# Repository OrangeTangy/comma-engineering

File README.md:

# comma.ai engineering portfolio — work in progress

This folder contains AI-assisted source, experiments and measured results for
the PCBGolf and original-CAN-core requests. **Neither requested project is
complete. These are work-in-progress portfolio artifacts, not a finalized
PCBGolf solution. No board has been fabricated or tested on hardware.**

## Reviewer entry points

- [Submission status and reproducibility](SUBMISSION.md): current evidence and known failures.
- [Classical CAN RTL and tests](can-core/README.md): simulation-tested bit-level engines.
- [PCBGolf layout experiments](pcbgolf/README.md): native KiCad projects and assembly exports.
- [Verification status](reports/STATUS.md): explicit completion gates.

## What works now

- `WORKING_PROMPT.md`: the prompt applied to guide the work.
- `can-core/`: original transmit/receive SystemVerilog bit-level engines, an
  independent polynomial-division Python oracle and deterministic simulation tests.
- `pcbgolf/`: source inventory, deterministic placement experiment, unchanged
  libraries, integrated schematics and editable KiCad placement/routing trials.
- `reports/`: tool logs and project status.

The CAN simulation suite passed 2,386 cases: 777 valid receive vectors, 770
transmit vectors, 496 receive fault/recovery cases, 100 back-to-back frames,
127 reset positions, 113 arbitration scenarios and three transmitter faults.
Twenty-six receive cases exercise a stuff bit immediately after the CRC sequence.
These are simulation results, not hardware or ISO compliance claims. Both RTL
modules also passed generic Yosys synthesis and structural checks with no
reported problems. FPGA mapping/timing remain unverified; see reports/STATUS.md.

The PCB placement experiment produced a 70 × 60 mm outline with all 245 original
footprints and their pad/net assignments retained. Its all-net half-perimeter
wirelength proxy decreased from 10,780.574 to 7,685.120 mm (28.71%). That is an
optimization of a proxy, **not a reduction in measured board score**. It has
zero routed tracks. Native KiCad now works: an assembly STEP was exported and
measured at 70 × 60 × 12.595 mm. This is an unrouted geometry measurement, not
a valid contest score. The integrated routing trial has repaired schematic
hierarchy and zero schematic/PCB parity errors; 499 unconnected items remain.

## Blocking completion

PCB: KiCad 10.0.6 runs from the local tools directory. The candidate still needs
mechanical/functional placement review, complete routing, native ERC/DRC,
fabrication-rule checks, assembly collision checks and an actual score. A leaderboard
entry would be misleading at this stage. Published prize deadline: October 12,
2026; current date: October 20. Late leaderboard acceptance is unconfirmed.

CAN: the core still needs bit timing/resynchronization, integrated bus access,
error frames/confinement/recovery, register/FIFO interface and FPGA constraints.
Extended CAN and CAN-FD are not implemented. No hardware is available.

The experiments suggest follow-up hypotheses, but an online search did not
establish that either is new. Existing work already includes AI placement,
autorouting, multi-board stacking and aggressive connector changes.

## Cheapest hardware starting point

As checked October 15, 2026: Tang Nano 9K was listed at $14.90 by Seeed, but out
of stock. It is a low-cost candidate for developing a small original controller;
a complete future CAN-FD design's fit and timing have not been established.
Sipeed documents its 8,640 LUT4 resources and onboard programming interface.
A Waveshare SN65HVD230 3.3 V Classical-CAN transceiver board was listed at $4.99.
That is about $20 excluding shipping, wiring and a second independent CAN node.
The SN65HVD230 is not the choice for validating high-rate CAN-FD.

Start with free simulation. Confirm FPGA fit and available seller inventory
before buying. Buy a CAN **transceiver** for the FPGA, not an MCP2515 controller
module that would implement the protocol externally. An independent MCU CAN
node or USB-CAN adapter is useful later as a reference peer.

Sources:
- https://wiki.sipeed.com/hardware/en/tang/Tang-Nano-9K/Nano-9K.html
- https://www.seeedstudio.com/tag/FPGA-Development-Board.html
- https://www.waveshare.com/product/sn65hvd230-can-board.htm
- https://github.com/commaai/PCBGolf
- https://comma.ai/leaderboard
- https://github.com/Logic-Design-Services/CTU-CAN-FD

## Application use

Do not describe this as a completed contest entry or an independently built,
production-ready CAN-FD controller. A defensible current description is:
“Developing an AI-assisted Classical CAN RTL prototype; I am reproducing and
reviewing its fault-injection tests and extending it toward hardware validation.”
Use that wording only after you have actually reproduced/reviewed the tests.
The final application should explain your own decisions, measurements and
contributions, with AI assistance disclosed accurately. No application email
has been prepared or sent.

Latest work (October 20): `pcbgolf/critical-trial/` groups 47 components by
circuit on the underside. It shortens critical switcher/clock pad distances and
has zero schematic-parity issues, but all 499 connections remain unrouted.
Its assembly envelope is 70.4 × 60.4 × 14.230 mm. The old placement's separate
`partial-route/` contains an incomplete routing diagnostic with 339 unconnected
items and six width violations. Neither is fabrication-ready or a submission.

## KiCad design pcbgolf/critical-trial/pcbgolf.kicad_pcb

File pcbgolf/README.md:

# PCBGolf engineering study

**Not a submission. No validated score.**

Upstream: https://github.com/commaai/PCBGolf
Revision: d0fd5a71087e3e10a49610f8c3e89912b4d20d77
Retrieved: 2026-10-15.

The upstream board contains 245 footprints, 1,078 pads, 302 named nets,
two copper layers, no track segments, no vias, no zones and no board outline.
Sixty-nine footprints have no courtyard geometry. Other courtyards can also be
incomplete; a nonzero vertex count is not evidence of validity.

## Run

```sh
python3 analyze.py /path/to/PCBGolf/pcbgolf.kicad_pcb --out baseline.json
python3 place.py /path/to/PCBGolf/pcbgolf.kicad_pcb candidate
```

`place.py` produces an **unrouted placement study**, preserving all components
and electrical assignments. It adds a 70 by 60 mm outline, fixes connector
anchors, uses a 12.85 by 7.0 mm envelope around each vertical OBD-C receptacle,
and packs geometry proxies with 0.25 mm separation. Signal-net span guides
placement and local optimization. High-degree nets are excluded from attraction
so a ground net does not collapse the placement; power and ground still require
explicit routing design. No decoupling, power-loop or thermal constraints are
implemented yet. The placement is therefore an experiment, not a recommended
layout. The current objective is HPWL, **not a congestion-aware routing model**.

`placement.svg` is a labeled **proxy** picture. Rectangle boundaries combine pad
bounds and available drawing geometry; they are not exact component bodies.
Missing courtyard/3D information is not repaired by the script. Connector
approach directions, ejected microSD clearance, probe access and simultaneous
plug fit need a real mechanical assembly check. In particular the fixed host
and barrel connector positions are hypotheses, not verified insertion paths.

`placement-results.json` reports actual surrogate metrics. HPWL is a wiring
estimate; it is not routed copper length or a leaderboard score. All parts remain
on the original layer with original rotation. `candidate/` carries the upstream
schematics, footprints and 3D component models with the experimental PCB.
Upstream files remain attributed to comma.ai; no ownership of them is claimed.

## Rules and current benchmark

https://github.com/commaai/PCBGolf/blob/master/README.md specifies assembled
bounding-box volume + 50 per via + 5,000 per copper layer. The prize deadline was
October 12, 2026. On October 15 the leaderboard still labels this a hiring
challenge and crosses out the cash prize. Scores range from 10,345 to 116,226.
Late submission acceptance has not been confirmed.

https://github.com/commaai/PCBGolf/issues/9 documents mandatory connector spacing,
simultaneous ports, retained 0.1-inch debug access, and acceptable SPI microSD.
Multi-board assemblies are allowed. Through-hole pads used only to change
layers count as vias. These constraints rule out several superficial shortcuts.

## Hypothesis and novelty

Optimize placement and MCU pin assignment together, then assess score only
among electrically and mechanically verified candidates. The present code
implements deterministic placement and net-identity auditing. It does **not**
implement legal MCU alternate-function reassignment, routing congestion,
routing, or a manufacturability certificate. Those are further work.

A search found published automated placement/routing and stacked-board attempts,
including https://silixon.io/blog/pcbgolf and the investigation at
https://github.com/tscircuit/tscircuit/issues/4948 . Thus “AI autorouting”, stacked
boards and changing connectors are not defensibly new on their own. No claim
that this approach has never been done online is justified by this search.

## Gates before submission

- Repair mechanical models/courtyards and verify all mating envelopes.
- Validate schematic equivalence and relevant input-voltage tolerances.
- Constrain decoupling, switcher loops, current paths, returns and USB pairs.
- Route all nets, fill planes, and run native KiCad ERC/DRC with no unexplained
  electrical violations or unconnected items.
- Verify JLCPCB fabrication capability against actual stackup and trace/drill rules.
- Export full assembly STEP, verify collisions/bounding box and calculate score.
- Review submission identity and package, then submit through the official form.

## Native verification update — October 19

KiCad 10.0.6 runs from a local app copy. `candidate-UNROUTED.step` and its PNG
are genuine native exports. The measured 70 × 60 × 12.595 mm assembly envelope
belongs only to the first unrouted candidate, not the later trials.

`routing-trial/` joins the five original standalone schematics into one hierarchy.
`integrate_schematics.py` preserves symbols/wires/global labels and repairs instance
paths. Native schematic/PCB parity now reports zero issues. Five redundant
host-connector SMD/PTH pad pairs were assigned their common physical terminal's
unused net; no functional signal was shorted. Twelve NC pads received explicit
unconnected-net names. BOM flags were aligned with the schematic.

The outline grew to 70.4 × 60.4 mm for edge clearance. Trial defaults are 0.15 mm
copper clearance, 0.20 mm hole clearance and 0.20 mm copper-to-edge clearance;
these are not a complete JLC fabrication rule set. Pre-route native DRC reports
129 warnings, zero other violations and **499 unconnected items**. Enabling the
upstream-disabled power-drive ERC check exposes **14 power-input errors** which
still need circuit review. Zero parity errors does not mean zero ERC errors.

`place_critical.py` creates a separate `critical-trial/` from the integrated
project. It moves selected regulator, crystal and bypass components underneath
and minimizes local pad distances subject to conservative body/pad rectangles.
It is a placement experiment, not a routed or thermally validated power layout.
No fabrication files or submission ZIP are offered.

### Critical-placement measurements

The first underside experiment moves 47 footprints (see `critical-placement.json`
for the exact inventory). Native checks report 139 warnings, 499 unconnected
items and zero schematic-parity issues. No non-connectivity errors were found;
this is not a clean routed DRC result. Bootstrap pad distances are 1.701 mm;
regulator switching-pin-to-inductor pad distances are 2.815 mm. These are straight
line XY distances, not routed lengths or electrical loop measurements.

The native assembly export `critical-UNROUTED.step` measures
70.4 × 60.4 × 14.230 mm, bounding volume 60,508.238 mm³. The underside adds
1.635 mm in height relative to the original assembly. Its geometry-only volume
plus two-layer penalty is 70,508.238, **before any via penalty**. This is not a
submission score: it has no routed interconnects or functional validation.

The original all-top routing experiment completed a first pass with 380 router
unrouted items and one router violation. Its internal score is unrelated to the
contest formula. The process later exited and saved a partial session on October 20. The placement
lacks sound critical-circuit grouping; completing its routing would not establish
function.

Reproduce the corrected integrated project on a copy of `candidate/`:

1. Run `prepare_routing.py COPY` with KiCad's Python.
2. Run `integrate_schematics.py COPY` with Python 3.
3. Export `COPY/pcbgolf.kicad_sch` as a KiCad XML netlist with `kicad-cli sch export netlist --format kicadxml`.
4. Run `prepare_routing.py COPY NETLIST.xml` with KiCad's Python.
5. Run `place_critical.py COPY NEW_COPY` with KiCad's Python.
6. Run native ERC, DRC with schematic parity, and STEP export on NEW_COPY.

Datasheet basis for keeping the switcher power components together:
https://www.diodes.com/datasheet/download/AP62300.pdf . The algorithm does not
yet implement the datasheet's routed copper, return-current or thermal layout.

### Imported partial route — October 20

`partial-route/` preserves the router's saved session on the old all-top layout.
Native KiCad reports 2,814 track segments, 437 vias, **339 unconnected items**,
zero schematic-parity issues, six track-width errors and 331 warnings. Six
router neck-down segments are 0.1000 mm, below the project's 0.1016 mm minimum.
The 199 dangling-via warnings further show that this is unfinished routing.
Do not fabricate this branch or combine its tracks with the moved components
in `critical-trial/`. The session was imported successfully, but the routing
experiment failed the completion gate. Native and router unrouted-item counts
use different definitions and must not be treated as interchangeable.

## Score estimates — October 20

`score.py BOARD.kicad_pcb ASSEMBLY.step` reports the bounding-box volume, vias,
copper layers and the formula total (it needs OCP / cadquery-ocp). See
[SCORE_ANALYSIS.md](SCORE_ANALYSIS.md): the unrouted critical trial is at least
70,569 and the four-layer trial at least 80,569. The barrel jack (11.0 mm) and
vertical OBD-C receptacles (8.8 mm) set the height, so routing alone cannot
make this layout competitive.

## Low-profile redesign — October 26

[GOLF_V2.md](GOLF_V2.md): horizontal OBD-C ports (JAE DX07, as already used for J3),
a mid-mount PJ-107AH-MSMT-TR jack in a board notch, two layers and two-sided placement.
Assembly height fell from 14.24 to 9.11 mm. The committed 58 × 56 mm board is partially
routed (160 vias, 213 unconnected items), so its 48,236 estimate is not a valid score.

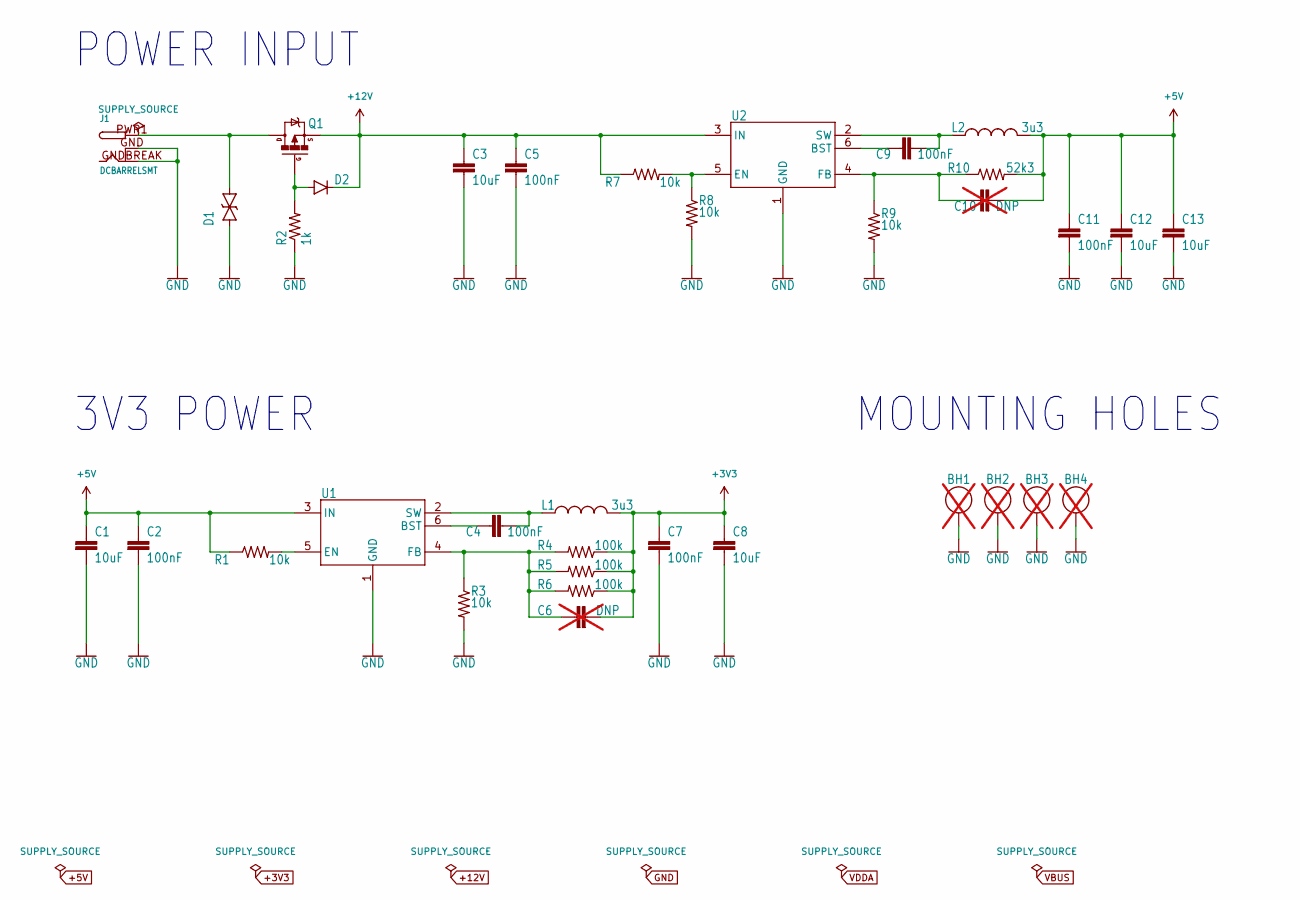
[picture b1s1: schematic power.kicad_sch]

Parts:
BH1, BH2, BH3, BH4: M2_BOLT; not fitted
C1, C3, C8, C12, C13: 10uF; 0805-C; MPN CL21A106KAYNNNE
C2, C4, C5, C7, C9, C11: 100nF; 0402-C; MPN CL05F104ZO5NNNC
C6, C10: DNP; 0402-C; not fitted
D1: TVS-BI-DO214AA; DO-214AA(SMB); MPN SMAJ16CA-13-F
D2: DIODEDB2W40100L; SOD-123F; MPN PMEG10020ELRX
J1: DCBARRELSMT; DCJACK_2MM_SMT; MPN PJ-002AH-SMT-TR
L1, L2: 3u3; L-1008; MPN MEKK2520T3R3M
Q1: SIS427-VI; PP-1212-8; MPN SI7101DN-T1-GE3
R1, R3, R7, R8, R9: 10k; 0402-R; MPN RC0402FR-0710KL
R2: 1k; 0402-R; MPN RC0402JR-071KL
R4, R5, R6: 100k; 0402-R; MPN RC0402JR-07100KL
R10: 52k3; 0402-R; MPN RC0402FR-0752K3L
U1, U2: AP62300T; SOT23-6; MPN AP62300WU-7

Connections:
+3V3: C6.2, C7.1, C8.1, L1.2, R4.1, R5.1, R6.1; also elsewhere on the board
+5V: C1.1, C2.1, C10.2, C11.1, C12.1, C13.1, L2.2, R1.1, R10.2, U1.3 (IN); also elsewhere on the board
+12V: C3.1, C5.1, D2.1 (C), Q1.1 (S), Q1.2 (S), Q1.3 (S), R7.1, U2.3 (IN); also elsewhere on the board
GND: BH1.0 (1_0), BH2.0 (1_0), BH3.0 (1_0), BH4.0 (1_0), C1.2, C2.2, C3.2, C5.2, C7.2, C8.2, C11.2, C12.2, C13.2, D1.1, J1.GND (GNDBREAK), J1.GNDBREAK (GND), R2.1, R3.2, R8.2, R9.2, U1.1 (GND), U2.1 (GND); also elsewhere on the board
unnamed: D2.2 (A), Q1.4 (G), R2.2
unnamed: D1.2, J1.PWR1 (PWR), Q1.5 (D), Q1.6 (D), Q1.7 (D), Q1.8 (D), Q1.9 (D)
unnamed: C4.1, U1.6 (BST)
unnamed: R1.2, U1.5 (EN)
unnamed: C6.1, R3.1, R4.2, R5.2, R6.2, U1.4 (FB)
unnamed: C4.2, L1.1, U1.2 (SW)
unnamed: C9.1, U2.6 (BST)
unnamed: R7.2, R8.1, U2.5 (EN)
unnamed: C10.1, R9.1, R10.1, U2.4 (FB)
unnamed: C9.2, L2.1, U2.2 (SW)

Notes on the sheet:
MOUNTING HOLES
3V3 POWER
POWER INPUT

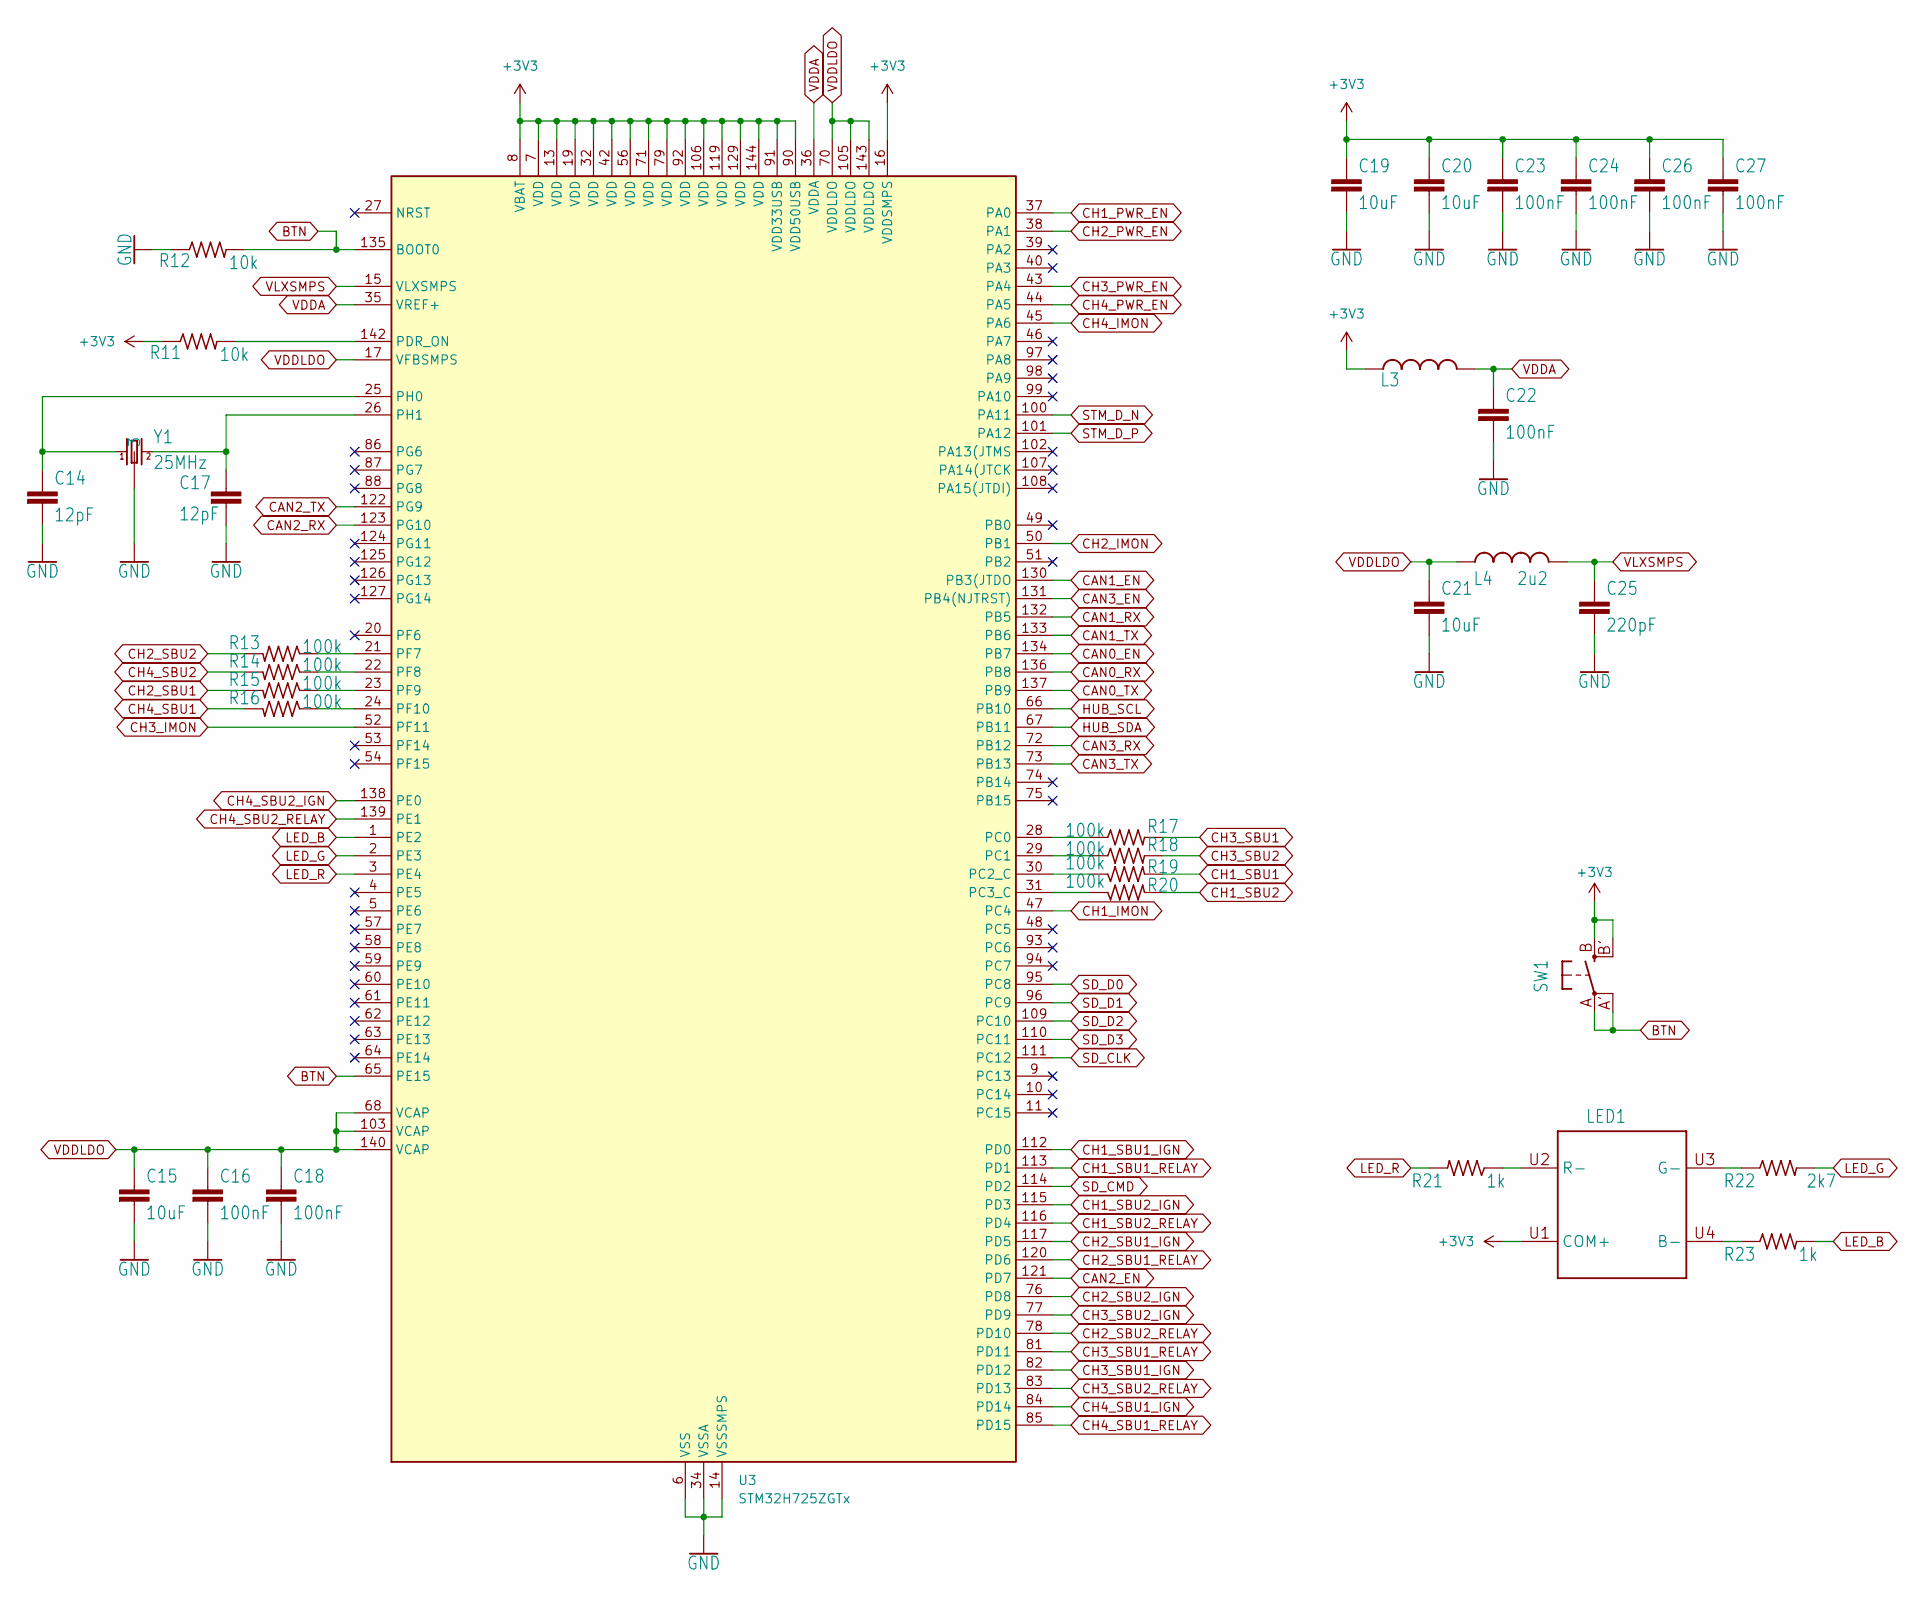
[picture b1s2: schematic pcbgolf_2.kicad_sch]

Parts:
C14, C17: 12pF; 0402-C; MPN C0402C120J5GACTU
C15, C19, C20, C21: 10uF; 0805-C; MPN CL21A106KAYNNNE
C16, C18, C22, C23, C24, C26, C27: 100nF; 0402-C; MPN CL05F104ZO5NNNC
C25: 220pF; 0402-C; MPN 04025A221FAT2A
L3: L-US-L2; 0603-L; MPN MH1608-601Y
L4: 2u2; 0806; MPN LQM2MPN2R2NG0L
LED1: CREE-RGB-CLMVC; MPN CLMVC-FKA-CL1D1L71BB7C3C3
R11, R12: 10k; 0402-R; MPN RC0402FR-0710KL
R13, R14, R15, R16, R17, R18, R19, R20: 100k; 0402-R; MPN RC0402JR-07100KL
R21, R23: 1k; 0402-R; MPN RC0402JR-071KL
R22: 2k7; 0402-R; MPN RC0402JR-072K7L
SW1: SPST-2-4PIN; EVQ-Q2; MPN EVQ-Q2Y03W
U3: STM32H725ZGTx; LQFP-144_20x20mm_P0.5mm; MPN STM32H725ZGT
Y1: 25MHz; XTAL-3.2X2.5; MPN RH100-25.000-12-F-1010-TR

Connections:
+3V3: C19.1, C20.1, C23.1, C24.1, C26.1, C27.1, L3.1, LED1.U1 (COM+), R11.1, SW1.B (S), SW1.B' (S1), U3.7 (VDD), U3.8 (VBAT), U3.13 (VDD), U3.16 (VDDSMPS), U3.19 (VDD), U3.32 (VDD), U3.42 (VDD), U3.56 (VDD), U3.71 (VDD), U3.79 (VDD), U3.90 (VDD50USB), U3.91 (VDD33USB), U3.92 (VDD), U3.106 (VDD), U3.119 (VDD), U3.129 (VDD), U3.144 (VDD); also elsewhere on the board
BTN: R12.2, SW1.A, SW1.A' (P1), U3.65 (PE15), U3.135 (BOOT0)
CAN0_EN: U3.134 (PB7); also elsewhere on the board
CAN0_RX: U3.136 (PB8); also elsewhere on the board
CAN0_TX: U3.137 (PB9); also elsewhere on the board
CAN1_EN: U3.130 (PB3(JTDO); also elsewhere on the board
CAN1_RX: U3.132 (PB5); also elsewhere on the board
CAN1_TX: U3.133 (PB6); also elsewhere on the board
CAN2_EN: U3.121 (PD7); also elsewhere on the board
CAN2_RX: U3.123 (PG10); also elsewhere on the board
CAN2_TX: U3.122 (PG9); also elsewhere on the board
CAN3_EN: U3.131 (PB4(NJTRST)); also elsewhere on the board
CAN3_RX: U3.72 (PB12); also elsewhere on the board
CAN3_TX: U3.73 (PB13); also elsewhere on the board
CH1_IMON: U3.47 (PC4); also elsewhere on the board
CH1_PWR_EN: U3.37 (PA0); also elsewhere on the board
CH1_SBU1: R19.2; also elsewhere on the board
CH1_SBU1_IGN: U3.112 (PD0); also elsewhere on the board
CH1_SBU1_RELAY: U3.113 (PD1); also elsewhere on the board
CH1_SBU2: R20.2; also elsewhere on the board
CH1_SBU2_IGN: U3.115 (PD3); also elsewhere on the board
CH1_SBU2_RELAY: U3.116 (PD4); also elsewhere on the board
CH2_IMON: U3.50 (PB1); also elsewhere on the board
CH2_PWR_EN: U3.38 (PA1); also elsewhere on the board
CH2_SBU1: R15.2; also elsewhere on the board
CH2_SBU1_IGN: U3.117 (PD5); also elsewhere on the board
CH2_SBU1_RELAY: U3.120 (PD6); also elsewhere on the board
CH2_SBU2: R13.2; also elsewhere on the board
CH2_SBU2_IGN: U3.76 (PD8); also elsewhere on the board
CH2_SBU2_RELAY: U3.78 (PD10); also elsewhere on the board
CH3_IMON: U3.52 (PF11); also elsewhere on the board
CH3_PWR_EN: U3.43 (PA4); also elsewhere on the board
CH3_SBU1: R17.2; also elsewhere on the board
CH3_SBU1_IGN: U3.82 (PD12); also elsewhere on the board
CH3_SBU1_RELAY: U3.81 (PD11); also elsewhere on the board
CH3_SBU2: R18.2; also elsewhere on the board
CH3_SBU2_IGN: U3.77 (PD9); also elsewhere on the board
CH3_SBU2_RELAY: U3.83 (PD13); also elsewhere on the board
CH4_IMON: U3.45 (PA6); also elsewhere on the board
CH4_PWR_EN: U3.44 (PA5); also elsewhere on the board
CH4_SBU1: R16.2; also elsewhere on the board
CH4_SBU1_IGN: U3.84 (PD14); also elsewhere on the board
CH4_SBU1_RELAY: U3.85 (PD15); also elsewhere on the board
CH4_SBU2: R14.2; also elsewhere on the board
CH4_SBU2_IGN: U3.138 (PE0); also elsewhere on the board
CH4_SBU2_RELAY: U3.139 (PE1); also elsewhere on the board
GND: C14.2, C15.2, C16.2, C17.2, C18.2, C19.2, C20.2, C21.2, C22.2, C23.2, C24.2, C25.2, C26.2, C27.2, R12.1, U3.6 (VSS), U3.12 (VSS), U3.14 (VSSSMPS), U3.18 (VSS), U3.33 (VSS), U3.34 (VSSA), U3.41 (VSS), U3.55 (VSS), U3.69 (VSS), U3.80 (VSS), U3.89 (VSS), U3.104 (VSS), U3.118 (VSS), U3.128 (VSS), U3.141 (VSS), Y1.2 (3), Y1.4 (3); also elsewhere on the board
HUB_SCL: U3.66 (PB10); also elsewhere on the board
HUB_SDA: U3.67 (PB11); also elsewhere on the board
LED_B: R23.2, U3.1 (PE2)
LED_G: R22.2, U3.2 (PE3)
LED_R: R21.2, U3.3 (PE4)
unnamed: LED1.U4 (B-), R23.1
unnamed: LED1.U3 (G-), R22.1
unnamed: LED1.U2 (R-), R21.1
unnamed: R17.1, U3.28 (PC0)
unnamed: R18.1, U3.29 (PC1)
unnamed: R19.1, U3.30 (PC2_C)
unnamed: R20.1, U3.31 (PC3_C)
unnamed: R11.2, U3.142 (PDR_ON)
unnamed: R13.1, U3.21 (PF7)
unnamed: R14.1, U3.22 (PF8)
unnamed: R15.1, U3.23 (PF9)
unnamed: R16.1, U3.24 (PF10)
unnamed: C14.1, U3.25 (PH0), Y1.1
unnamed: C17.1, U3.26 (PH1), Y1.3 (2)
SD_CLK: U3.111 (PC12); also elsewhere on the board
SD_CMD: U3.114 (PD2); also elsewhere on the board
SD_D0: U3.95 (PC8); also elsewhere on the board
SD_D1: U3.96 (PC9); also elsewhere on the board
SD_D2: U3.109 (PC10); also elsewhere on the board
SD_D3: U3.110 (PC11); also elsewhere on the board
STM_D_N: U3.100 (PA11); also elsewhere on the board
STM_D_P: U3.101 (PA12); also elsewhere on the board
VDDA: C22.1, L3.2, U3.35 (VREF+), U3.36 (VDDA)
VDDLDO: C15.1, C16.1, C18.1, C21.1, L4.1, U3.17 (VFBSMPS), U3.68 (VCAP), U3.70 (VDDLDO), U3.103 (VCAP), U3.105 (VDDLDO), U3.140 (VCAP), U3.143 (VDDLDO)
VLXSMPS: C25.1, L4.2, U3.15 (VLXSMPS)

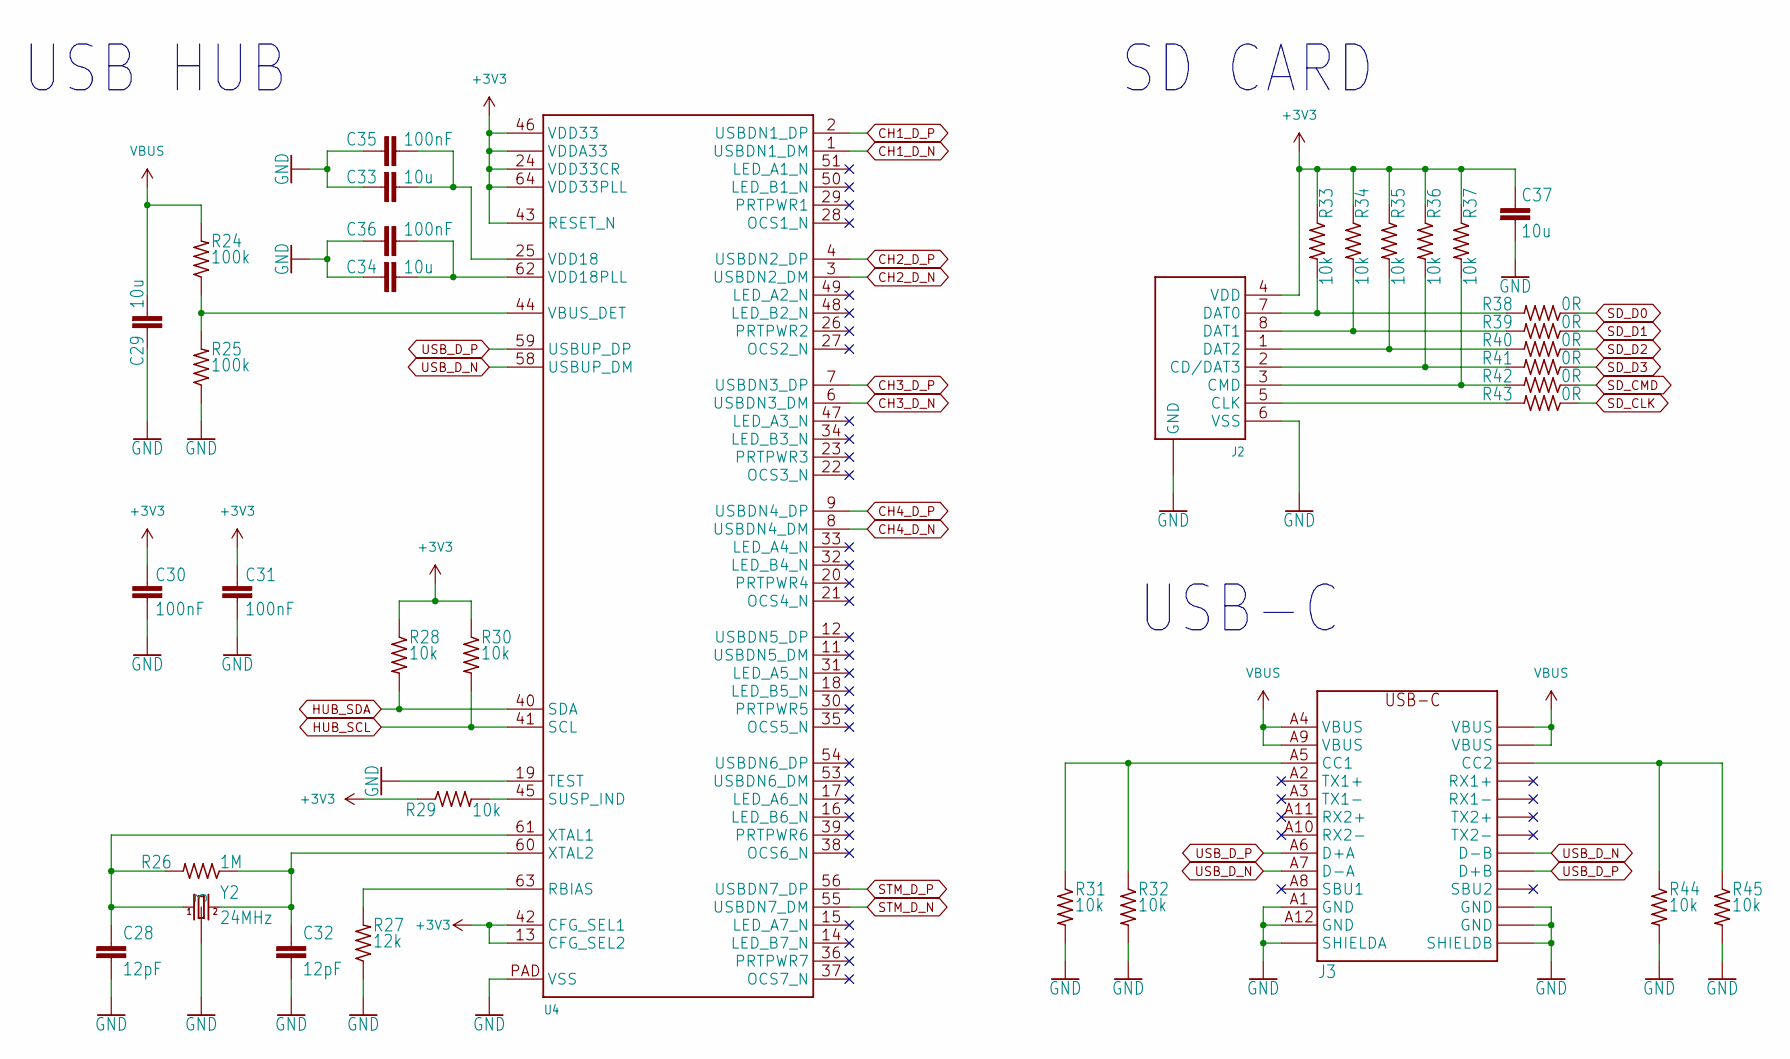
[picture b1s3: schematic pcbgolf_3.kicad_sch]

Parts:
C28, C32: 12pF; 0402-C; MPN C0402C120J5GACTU
C29, C33, C34, C37: 10u; 0402-C; MPN GRM155R61A106ME11D
C30, C31, C35, C36: 100nF; 0402-C; MPN CL05F104ZO5NNNC
J2: MICRO_SD-0472192001; 0472192001; MPN 47219-2001
J3: USB-C-FEMALE; DX07S024XJ1R1100; MPN DX07S024XJ1R1100
R24, R25: 100k; 0402-R; MPN RC0402JR-07100KL
R26: 1M; 0402-R; MPN RC0402JR-071ML
R27: 12k; 0402-R; MPN CRGCQ0402F12K
R28, R29, R30, R31, R32, R33, R34, R35, R36, R37, R44, R45: 10k; 0402-R; MPN RC0402FR-0710KL
R38, R39, R40, R41, R42, R43: 0R; 0402-R; MPN RMCF0402ZT0R00
U4: USB2517; QFN64-9X9; MPN USB2517
Y2: 24MHz; XTAL-3.2X2.5; MPN ABM8AIG-24.000MHZ-12-2Z-T3

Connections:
+3V3: C30.2, C31.2, C37.1, J2.4 (VDD), R28.1, R29.1, R30.1, R33.1, R34.1, R35.1, R36.1, R37.1, U4.5 (VDDA33), U4.10 (VDDA33), U4.13 (CFG_SEL2), U4.24 (VDD33CR), U4.42 (CFG_SEL1), U4.43 (RESET_N), U4.46 (VDD33), U4.52 (VDDA33), U4.57 (VDDA33), U4.64 (VDD33PLL); also elsewhere on the board
CH1_D_N: U4.1 (USBDN1_DM); also elsewhere on the board
CH1_D_P: U4.2 (USBDN1_DP); also elsewhere on the board
CH2_D_N: U4.3 (USBDN2_DM); also elsewhere on the board
CH2_D_P: U4.4 (USBDN2_DP); also elsewhere on the board
CH3_D_N: U4.6 (USBDN3_DM); also elsewhere on the board
CH3_D_P: U4.7 (USBDN3_DP); also elsewhere on the board
CH4_D_N: U4.8 (USBDN4_DM); also elsewhere on the board
CH4_D_P: U4.9 (USBDN4_DP); also elsewhere on the board
GND: C28.2, C29.2, C30.1, C31.1, C32.2, C33.2, C34.2, C35.1, C36.1, C37.2, J2.6 (VSS), J2.G1 (GND), J2.G2 (GND), J2.G3 (GND), J2.G4 (GND), J3.A1 (GND), J3.A12 (GND), J3.B1 (GND), J3.B1T (GND), J3.B12 (GND), J3.B12T (GND), J3.S1B (SHIELDA), J3.S1T (SHIELDA), J3.S1TH (SHIELDA), J3.S2B (SHIELDA), J3.S2T (SHIELDA), J3.S2TH (SHIELDA), J3.S3B (SHIELDB), J3.S3T (SHIELDB), J3.S3TH (SHIELDB), J3.S4B (SHIELDB), J3.S4T (SHIELDB), J3.S4TH (SHIELDB), R25.1, R27.1, R31.2, R32.2, R44.2, R45.2, U4.19 (TEST), U4.PAD (VSS), Y2.2 (3), Y2.4 (3); also elsewhere on the board
HUB_SCL: R30.2, U4.41 (SCL); also elsewhere on the board
HUB_SDA: R28.2, U4.40 (SDA); also elsewhere on the board
unnamed: J2.2 (CD/DAT3), R36.2, R41.2
unnamed: J2.5 (CLK), R43.2
unnamed: J2.3 (CMD), R37.2, R42.2
unnamed: J2.7 (DAT0), R33.2, R38.2
unnamed: J2.8 (DAT1), R34.2, R39.2
unnamed: J2.1 (DAT2), R35.2, R40.2
unnamed: J3.A5 (CC1), R31.1, R32.1
unnamed: J3.B5 (CC2), J3.B5T (CC2), R44.1, R45.1
unnamed: R27.2, U4.63 (RBIAS)
unnamed: R29.2, U4.45 (SUSP_IND)
unnamed: R24.1, R25.2, U4.44 (VBUS_DET)
unnamed: C33.1, C35.2, U4.25 (VDD18)
unnamed: C34.1, C36.2, U4.62 (VDD18PLL)
unnamed: C28.1, R26.2, U4.61 (XTAL1), Y2.1
unnamed: C32.1, R26.1, U4.60 (XTAL2), Y2.3 (2)
SD_CLK: R43.1; also elsewhere on the board
SD_CMD: R42.1; also elsewhere on the board
SD_D0: R38.1; also elsewhere on the board
SD_D1: R39.1; also elsewhere on the board
SD_D2: R40.1; also elsewhere on the board
SD_D3: R41.1; also elsewhere on the board
STM_D_N: U4.55 (USBDN7_DM); also elsewhere on the board
STM_D_P: U4.56 (USBDN7_DP); also elsewhere on the board
USB_D_N: J3.A7 (D-A), J3.B7 (D-B), J3.B7T (D-B), U4.58 (USBUP_DM)
USB_D_P: J3.A6 (D+A), J3.B6 (D+B), J3.B6T (D+B), U4.59 (USBUP_DP)
VBUS: C29.1, J3.A4 (VBUS), J3.A9 (VBUS), J3.B4 (VBUS), J3.B4T (VBUS), J3.B9 (VBUS), J3.B9T (VBUS), R24.2

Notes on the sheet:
SD CARD
USB-C
USB HUB

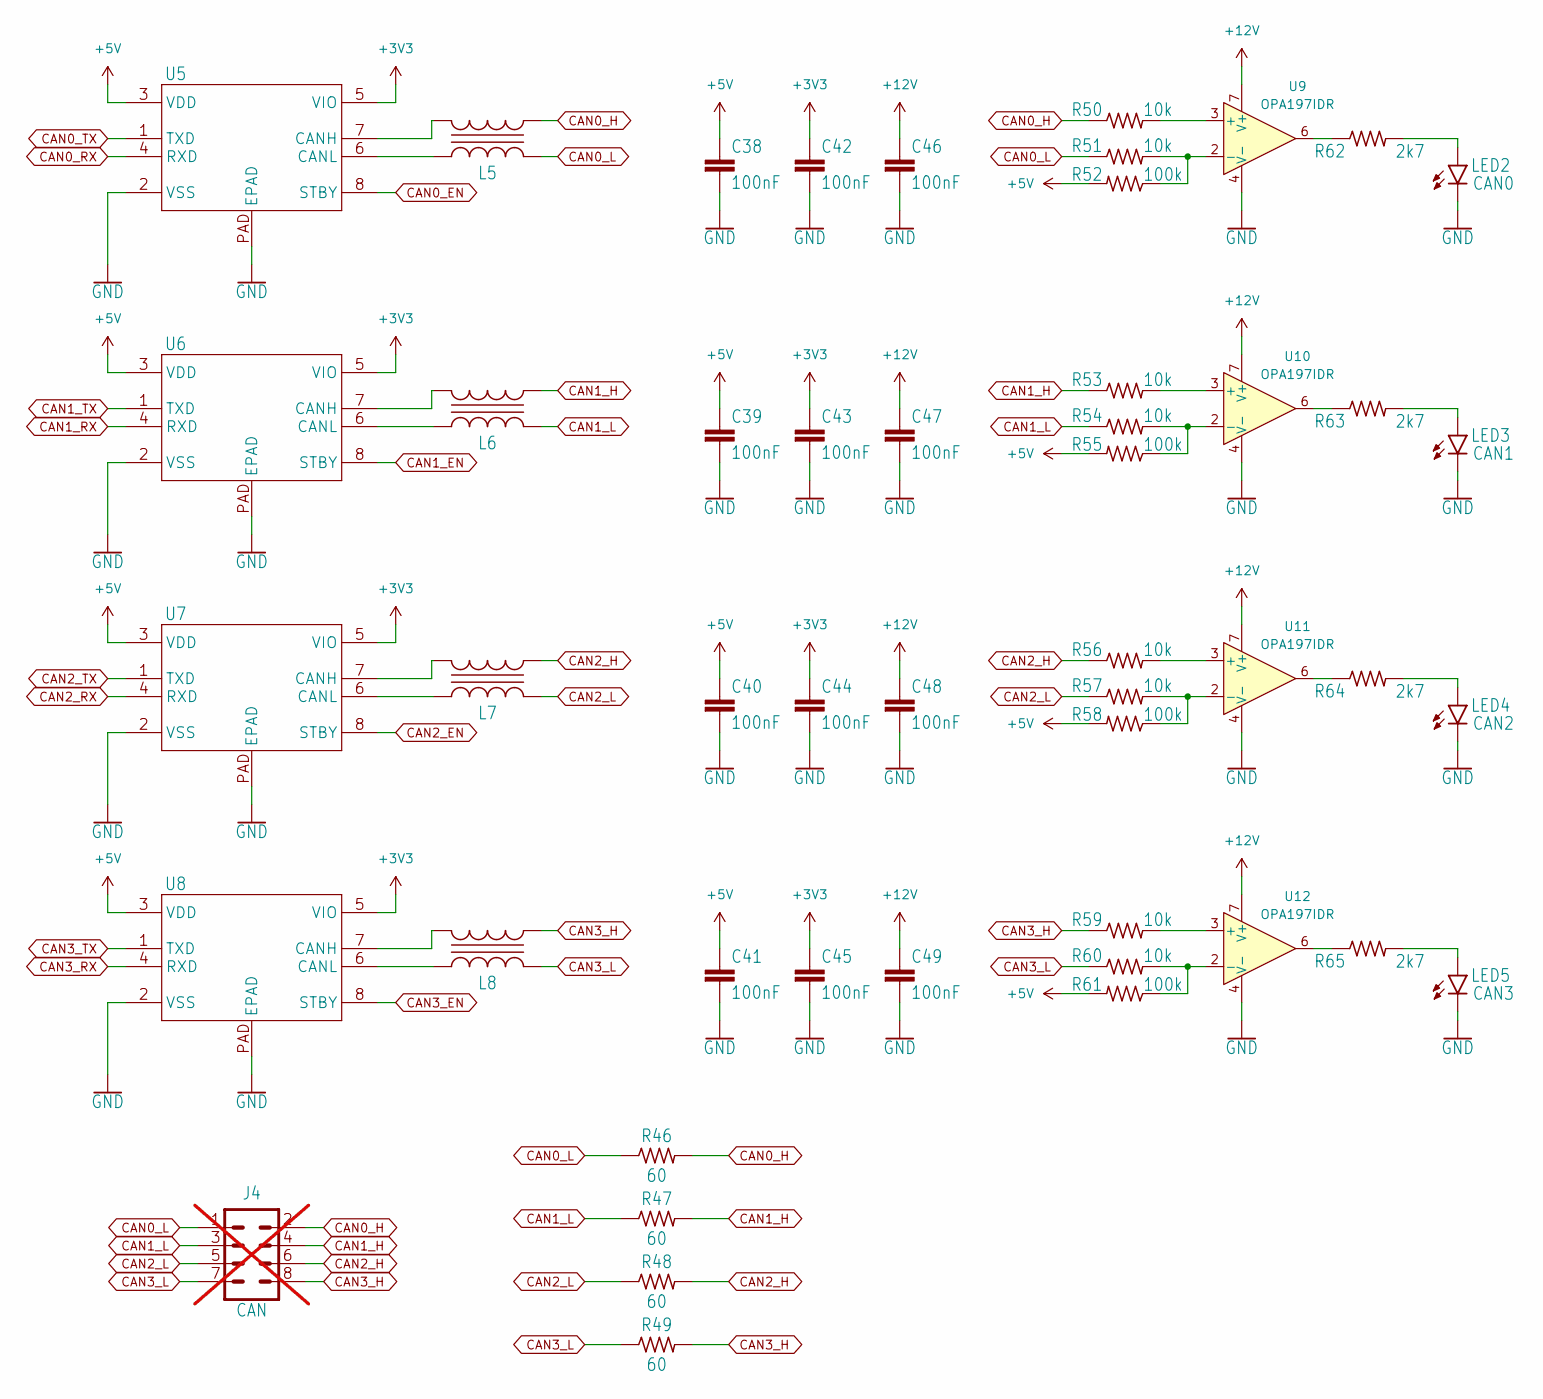
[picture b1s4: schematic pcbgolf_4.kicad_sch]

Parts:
C38, C39, C40, C41, C42, C43, C44, C45, C46, C47, C48, C49: 100nF; 0402-C; MPN CL05F104ZO5NNNC
J4: CAN; 2X04; not fitted
L5, L6, L7, L8: ACT1210D_CHOKE; CHOKE-3.2X2.5; MPN ACT1210D-101-2P-TL00
LED2: CAN0; CHIPLED; MPN LG R971-KN-1
LED3: CAN1; CHIPLED; MPN LG R971-KN-1
LED4: CAN2; CHIPLED; MPN LG R971-KN-1
LED5: CAN3; CHIPLED; MPN LG R971-KN-1
R46, R47, R48, R49: 60; 0402-R; MPN RC0402FR-0760R4L
R50, R51, R53, R54, R56, R57, R59, R60: 10k; 0402-R; MPN RC0402FR-0710KL
R52, R55, R58, R61: 100k; 0402-R; MPN RC0402JR-07100KL
R62, R63, R64, R65: 2k7; 0402-R; MPN RC0402JR-072K7L
U5, U6, U7, U8: MCP2542FDT-E/MNY; TDFN8_2X3MC_MCH; MPN MCP2542FDT-H/MNY
U9, U10, U11, U12: OPA197IDR; SOIC-8_3.9x4.9mm_P1.27mm; MPN OPA197IDR

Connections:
+3V3: C42.1, C43.1, C44.1, C45.1, U5.5 (VIO), U6.5 (VIO), U7.5 (VIO), U8.5 (VIO); also elsewhere on the board
+5V: C38.1, C39.1, C40.1, C41.1, R52.2, R55.2, R58.2, R61.2, U5.3 (VDD), U6.3 (VDD), U7.3 (VDD), U8.3 (VDD); also elsewhere on the board
+12V: C46.1, C47.1, C48.1, C49.1, U9.7 (V+), U10.7 (V+), U11.7 (V+), U12.7 (V+); also elsewhere on the board
CAN0_EN: U5.8 (STBY); also elsewhere on the board
CAN0_H: J4.2, L5.4, R46.2, R50.1; also elsewhere on the board
CAN0_L: J4.1, L5.3, R46.1, R51.1; also elsewhere on the board
CAN0_RX: U5.4 (RXD); also elsewhere on the board
CAN0_TX: U5.1 (TXD); also elsewhere on the board
CAN1_EN: U6.8 (STBY); also elsewhere on the board
CAN1_H: J4.4, L6.4, R47.2, R53.1; also elsewhere on the board
CAN1_L: J4.3, L6.3, R47.1, R54.1; also elsewhere on the board
CAN1_RX: U6.4 (RXD); also elsewhere on the board
CAN1_TX: U6.1 (TXD); also elsewhere on the board
CAN2_EN: U7.8 (STBY); also elsewhere on the board
CAN2_H: J4.6, L7.4, R48.2, R56.1; also elsewhere on the board
CAN2_L: J4.5, L7.3, R48.1, R57.1; also elsewhere on the board
CAN2_RX: U7.4 (RXD); also elsewhere on the board
CAN2_TX: U7.1 (TXD); also elsewhere on the board
CAN3_EN: U8.8 (STBY); also elsewhere on the board
CAN3_H: J4.8, L8.4, R49.2, R59.1; also elsewhere on the board
CAN3_L: J4.7, L8.3, R49.1, R60.1; also elsewhere on the board
CAN3_RX: U8.4 (RXD); also elsewhere on the board
CAN3_TX: U8.1 (TXD); also elsewhere on the board
GND: C38.2, C39.2, C40.2, C41.2, C42.2, C43.2, C44.2, C45.2, C46.2, C47.2, C48.2, C49.2, LED2.C, LED3.C, LED4.C, LED5.C, U5.2 (VSS), U5.PAD (EPAD), U6.2 (VSS), U6.PAD (EPAD), U7.2 (VSS), U7.PAD (EPAD), U8.2 (VSS), U8.PAD (EPAD), U9.4 (V-), U10.4 (V-), U11.4 (V-), U12.4 (V-); also elsewhere on the board
unnamed: LED2.A, R62.2
unnamed: LED3.A, R63.2
unnamed: LED4.A, R64.2
unnamed: LED5.A, R65.2
unnamed: R62.1, U9.6
unnamed: R63.1, U10.6
unnamed: R64.1, U11.6
unnamed: R65.1, U12.6
unnamed: L5.1, U5.7 (CANH)
unnamed: L5.2, U5.6 (CANL)
unnamed: L6.1, U6.7 (CANH)
unnamed: L6.2, U6.6 (CANL)
unnamed: L7.1, U7.7 (CANH)
unnamed: L7.2, U7.6 (CANL)
unnamed: L8.1, U8.7 (CANH)
unnamed: L8.2, U8.6 (CANL)
unnamed: R50.2, U9.3 (+)
unnamed: R51.2, R52.1, U9.2 (-)
unnamed: R53.2, U10.3 (+)
unnamed: R54.2, R55.1, U10.2 (-)
unnamed: R56.2, U11.3 (+)
unnamed: R57.2, R58.1, U11.2 (-)
unnamed: R59.2, U12.3 (+)
unnamed: R60.2, R61.1, U12.2 (-)
